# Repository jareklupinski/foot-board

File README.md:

# foot-board
A USB Keyboard Device, laid out to be used with your Feet

Uses Kailh Low Profile Switches, code written to be easy to jump into and modify.

Can be produced by JLCPCB for extremely low cost. Only thing they cannot do is solder the MicroUSB jack; considering laying out the PCB with a connector for an off-the-shelf Blue Pill board to fix.

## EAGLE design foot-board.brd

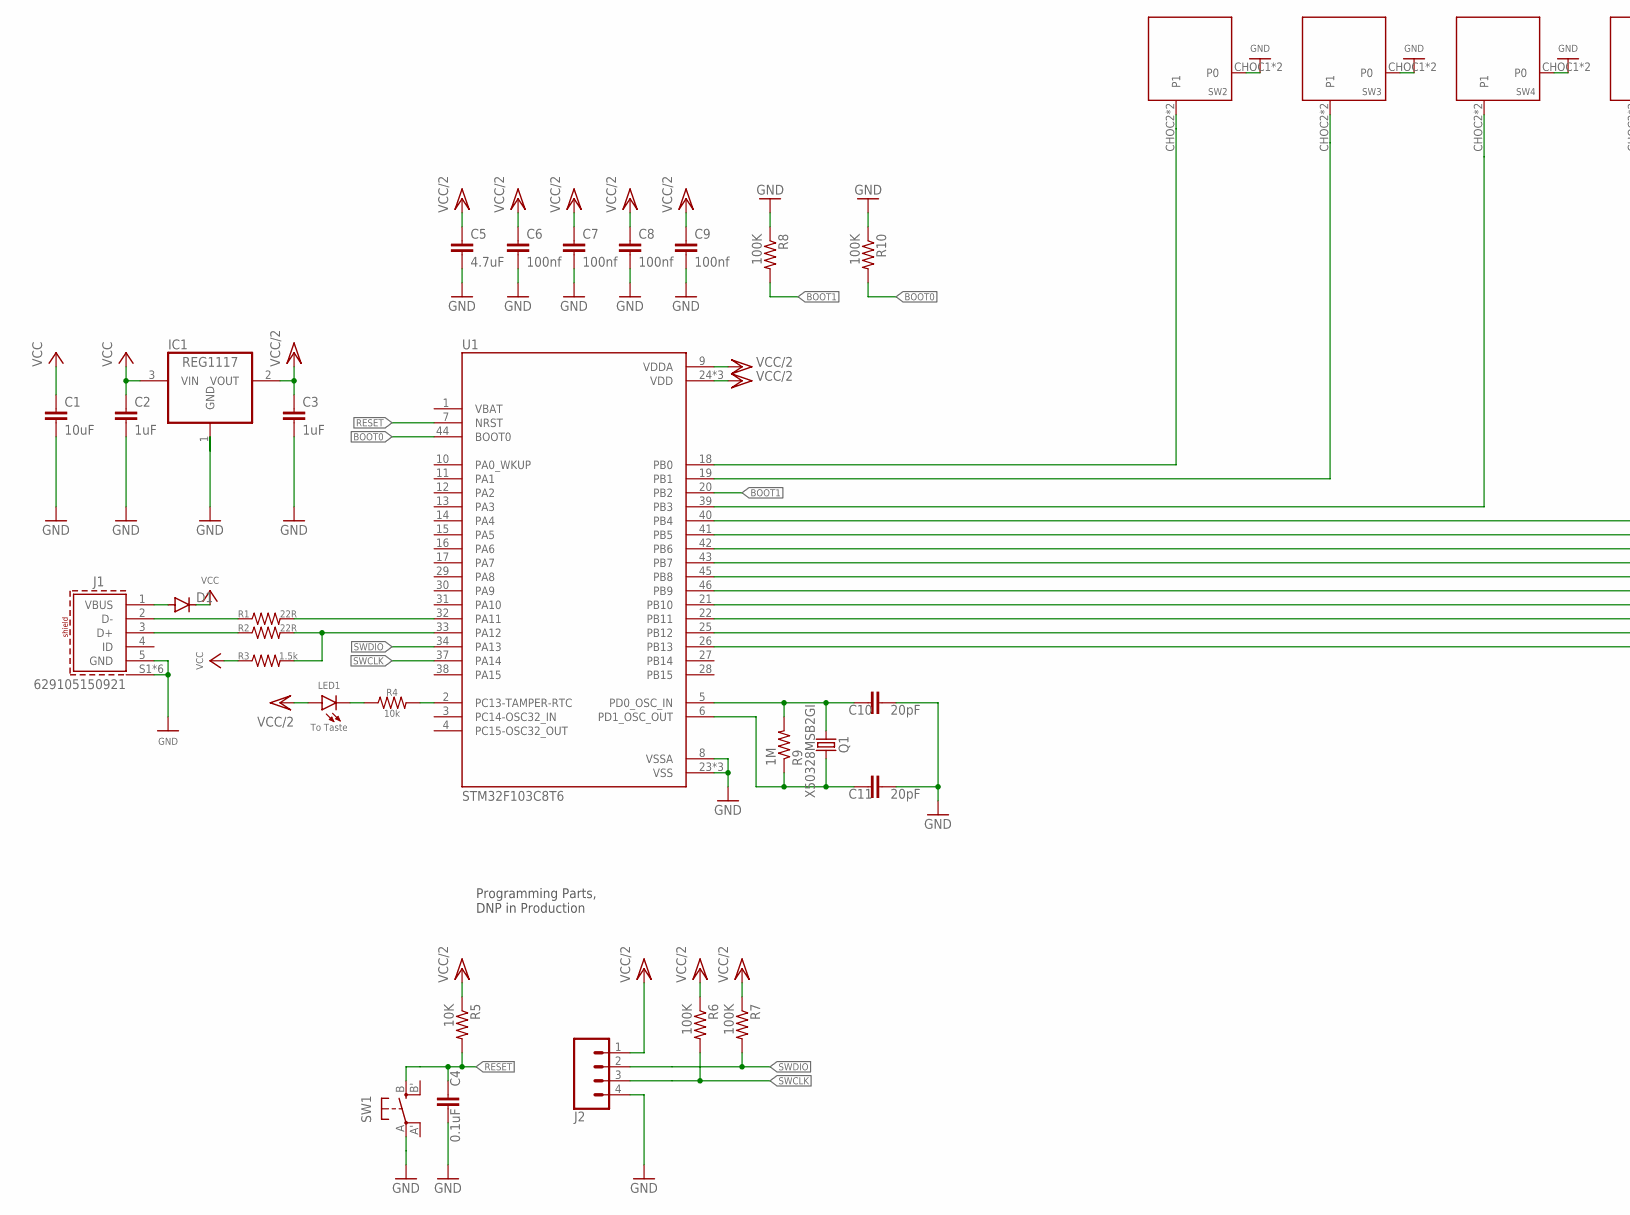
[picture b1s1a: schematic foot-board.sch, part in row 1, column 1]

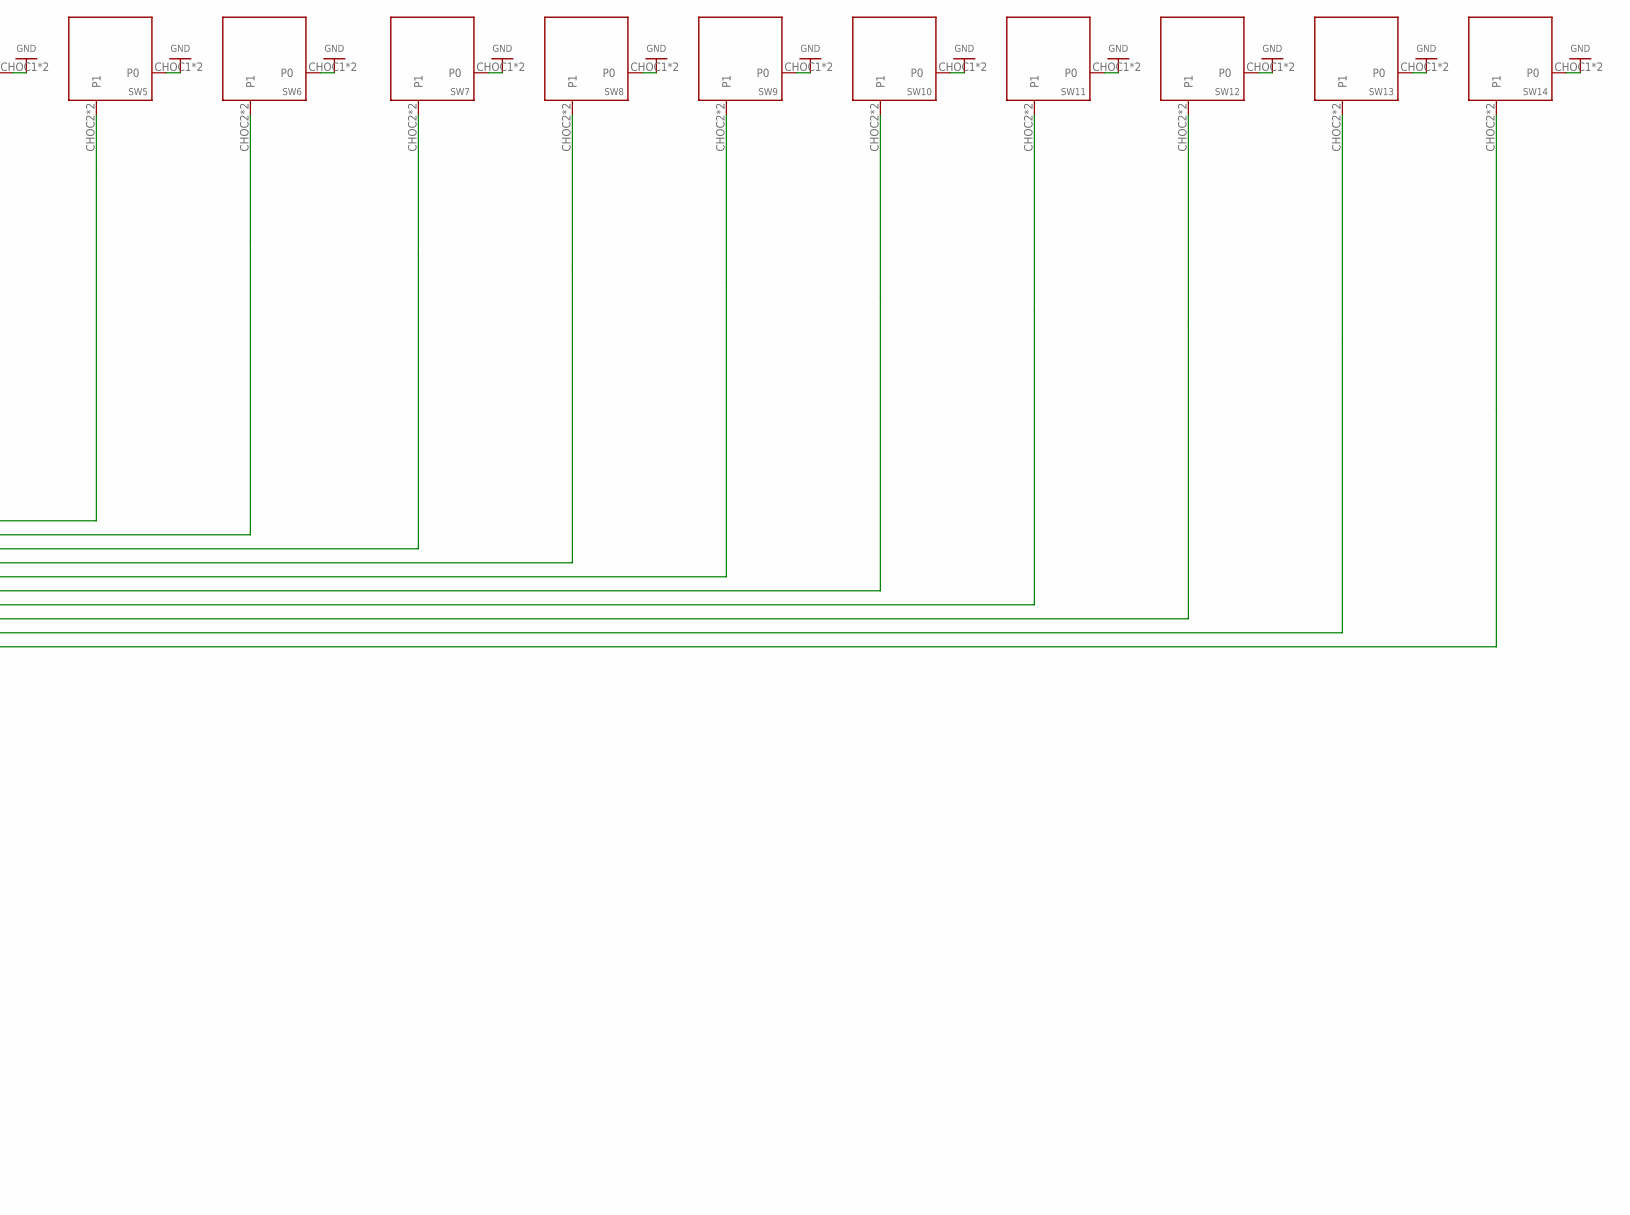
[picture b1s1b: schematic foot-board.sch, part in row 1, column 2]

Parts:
C1: 10uF; C0805
C2, C3: 1uF; C0402
C4: 0.1uF; C0402
C5: 4.7uF; C0805
C6, C7, C8, C9: 100nf; C0402
C10, C11: 20pF; C0402
D1: DIODE-DO214AC; DO214AC
IC1: REG1117; SOT223
J1: 629105150921
J2: CONN_04; 1X04
LED1: To Taste; CHIPLED_0603
Q1: X50328MSB2GI; 6.0X3.5_2
R1, R2: 22R; R0402
R3: 1.5k; R0402
R4: 10k; R0402
R5: 10K; R0402
R6, R7, R8, R10: 100K; R0402
R9: 1M; R0402
SW1: SPST_TACT-EVQQ2; EVQ-Q2
SW2, SW3, SW4, SW5, SW6, SW7, SW8, SW9, SW10, SW11, SW12, SW13, SW14: KEYSWITCH-PLAIN-CHOCX-1U; CHOCX-1U
U1: STM32F103C8T6; QFP50P900X900X160-48N

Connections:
BOOT0: R10.2, U1.44 (BOOT0)
BOOT1: R8.2, U1.20 (PB2)
GND: C1.2, C2.2, C3.2, C4.2, C5.2, C6.2, C7.2, C8.2, C9.2, C10.2, C11.2, IC1.1 (GND), J1.5 (GND), J1.S1 (SHIELD), J1.S2 (SHIELD), J1.S3 (SHIELD), J1.S4 (SHIELD), J1.S5 (SHIELD), J1.S6 (SHIELD), J2.4, R8.1, R10.1, SW1.A, SW2.CHOC1 (P0), SW2.X1 (P0), SW3.CHOC1 (P0), SW3.X1 (P0), SW4.CHOC1 (P0), SW4.X1 (P0), SW5.CHOC1 (P0), SW5.X1 (P0), SW6.CHOC1 (P0), SW6.X1 (P0), SW7.CHOC1 (P0), SW7.X1 (P0), SW8.CHOC1 (P0), SW8.X1 (P0), SW9.CHOC1 (P0), SW9.X1 (P0), SW10.CHOC1 (P0), SW10.X1 (P0), SW11.CHOC1 (P0), SW11.X1 (P0), SW12.CHOC1 (P0), SW12.X1 (P0), SW13.CHOC1 (P0), SW13.X1 (P0), SW14.CHOC1 (P0), SW14.X1 (P0), U1.8 (VSSA), U1.23 (VSS), U1.35 (VSS), U1.47 (VSS)
unnamed: R4.2, U1.2 (PC13-TAMPER-RTC)
unnamed: LED1.C, R4.1
unnamed: SW2.CHOC2 (P1), SW2.X2 (P1), U1.18 (PB0)
unnamed: R1.2, U1.32 (PA11)
unnamed: D1.A, J1.1 (VBUS)
unnamed: R2.2, R3.2, U1.33 (PA12)
unnamed: SW3.CHOC2 (P1), SW3.X2 (P1), U1.19 (PB1)
unnamed: SW4.CHOC2 (P1), SW4.X2 (P1), U1.39 (PB3)
unnamed: SW5.CHOC2 (P1), SW5.X2 (P1), U1.40 (PB4)
unnamed: SW6.CHOC2 (P1), SW6.X2 (P1), U1.41 (PB5)
unnamed: SW7.CHOC2 (P1), SW7.X2 (P1), U1.42 (PB6)
unnamed: SW8.CHOC2 (P1), SW8.X2 (P1), U1.43 (PB7)
unnamed: SW9.CHOC2 (P1), SW9.X2 (P1), U1.45 (PB8)
unnamed: SW10.CHOC2 (P1), SW10.X2 (P1), U1.46 (PB9)
unnamed: SW11.CHOC2 (P1), SW11.X2 (P1), U1.21 (PB10)
unnamed: J1.2 (D-), R1.1
unnamed: J1.3 (D+), R2.1
unnamed: SW12.CHOC2 (P1), SW12.X2 (P1), U1.22 (PB11)
unnamed: SW13.CHOC2 (P1), SW13.X2 (P1), U1.25 (PB12)
unnamed: SW14.CHOC2 (P1), SW14.X2 (P1), U1.26 (PB13)
unnamed: C10.1, Q1.2, R9.2, U1.5 (PD0_OSC_IN)
unnamed: C11.1, Q1.1, R9.1, U1.6 (PD1_OSC_OUT)
RESET: C4.1, R5.2, SW1.B (S), U1.7 (NRST)
SWCLK: J2.3, R6.2, U1.37 (PA14)
SWDIO: J2.2, R7.2, U1.34 (PA13)
VCC: C1.1, C2.1, D1.C, IC1.3 (VIN), R3.1
VCC/2: C3.1, C5.1, C6.1, C7.1, C8.1, C9.1, IC1.2 (VOUT), J2.1, LED1.A, R5.1, R6.1, R7.1, U1.9 (VDDA), U1.24 (VDD), U1.36 (VDD), U1.48 (VDD)

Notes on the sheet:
Programming Parts, DNP in Production

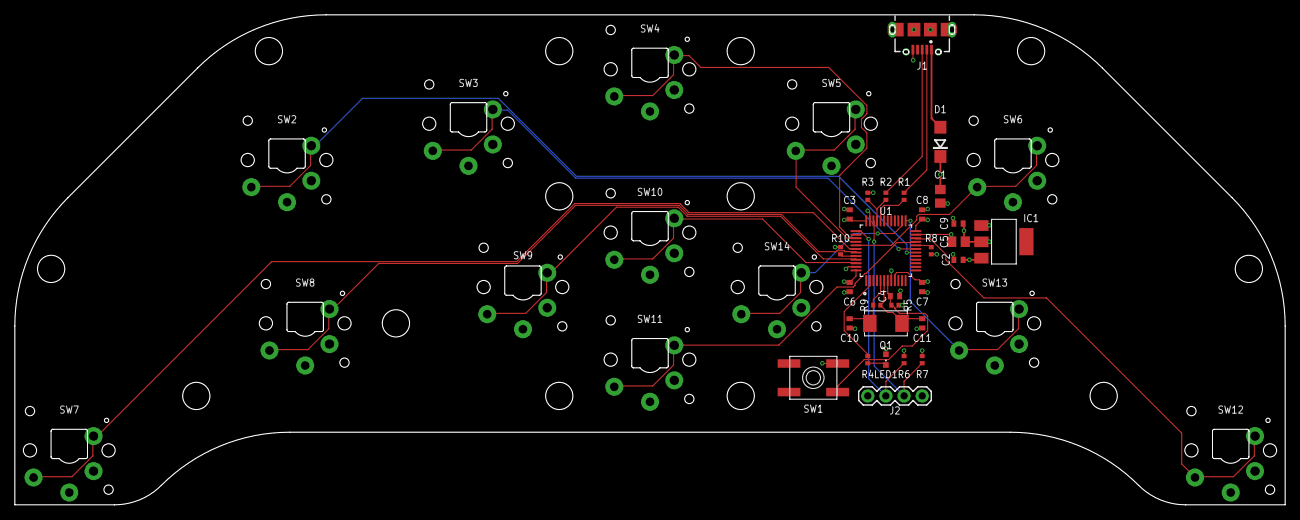
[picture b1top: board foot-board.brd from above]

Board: 4 copper layers, 177.8 x 68.6 mm, 42 parts (0 on the bottom side), 30 nets.

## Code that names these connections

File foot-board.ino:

#include "Keyboard.h"

void setup() {
  pinMode(PB0, INPUT_PULLUP);
  pinMode(PB1, INPUT_PULLUP);
  pinMode(PB3, INPUT_PULLUP);
  pinMode(PB4, INPUT_PULLUP);
  pinMode(PB5, INPUT_PULLUP);
  pinMode(PB6, INPUT_PULLUP);
  pinMode(PB7, INPUT_PULLUP);
  pinMode(PB8, INPUT_PULLUP);
  pinMode(PB9, INPUT_PULLUP);
  pinMode(PB10, INPUT_PULLUP);
  pinMode(PB11, INPUT_PULLUP);
  pinMode(PB12, INPUT_PULLUP);
  pinMode(PB13, INPUT_PULLUP);
  pinMode(PC13, OUTPUT);
  Keyboard.begin();
  digitalWrite(PC13, LOW);
}

byte button1Pressed = 0;
byte button2Pressed = 0;
byte button3Pressed = 0;
byte button4Pressed = 0;
byte button5Pressed = 0;
byte button6Pressed = 0;
byte button7Pressed = 0;
byte button8Pressed = 0;
byte button9Pressed = 0;
byte button10Pressed = 0;
byte button11Pressed = 0;
byte button12Pressed = 0;
byte button13Pressed = 0;

void loop() {
  byte newButton1Pressed = 0;
  if ( digitalReadFast(PB_0) ) newButton1Pressed = 1;
  if ( newButton1Pressed != button1Pressed ) {
    newButton1Pressed ? Keyboard.release('1') : Keyboard.press('1');
    button1Pressed = newButton1Pressed;
  }
  byte newButton2Pressed = 0;
  if ( digitalReadFast(PB_1) ) newButton2Pressed = 1;
  if ( newButton2Pressed != button2Pressed ) {
    newButton2Pressed ? Keyboard.release('2') : Keyboard.press('2');
    button2Pressed = newButton2Pressed;
  }
  byte newButton3Pressed = 0;
  if ( digitalReadFast(PB_3) ) newButton3Pressed = 1;
  if ( newButton3Pressed != button3Pressed ) {
    newButton3Pressed ? Keyboard.release('3') : Keyboard.press('3');
    button3Pressed = newButton3Pressed;
  }
  byte newButton4Pressed = 0;
  if ( digitalReadFast(PB_4) ) newButton4Pressed = 1;
  if ( newButton4Pressed != button4Pressed ) {
    newButton4Pressed ? Keyboard.release('4') : Keyboard.press('4');
    button4Pressed = newButton4Pressed;
  }
  byte newButton5Pressed = 0;
  if ( digitalReadFast(PB_5) ) newButton5Pressed = 1;
  if ( newButton5Pressed != button5Pressed ) {
    newButton5Pressed ? Keyboard.release('5') : Keyboard.press('5');
    button5Pressed = newButton5Pressed;
  }
  byte newButton6Pressed = 0;
  if ( digitalReadFast(PB_6) ) newButton6Pressed = 1;
  if ( newButton6Pressed != button6Pressed ) {
    newButton6Pressed ? Keyboard.release('z') : Keyboard.press('z');
    button6Pressed = newButton6Pressed;
  }
  byte newButton7Pressed = 0;
  if ( digitalReadFast(PB_7) ) newButton7Pressed = 1;
  if ( newButton7Pressed != button7Pressed ) {
    newButton7Pressed ? Keyboard.release('x') : Keyboard.press('x');
    button7Pressed = newButton7Pressed;
  }
  byte newButton8Pressed = 0;
  if ( digitalReadFast(PB_8) ) newButton8Pressed = 1;
  if ( newButton8Pressed != button8Pressed ) {
    newButton8Pressed ? Keyboard.release(KEY_LEFT_ARROW) : Keyboard.press(KEY_LEFT_ARROW);
    button8Pressed = newButton8Pressed;
  }
  byte newButton9Pressed = 0;
  if ( digitalReadFast(PB_9) ) newButton9Pressed = 1;
  if ( newButton9Pressed != button9Pressed ) {
    newButton9Pressed ? Keyboard.release(KEY_UP_ARROW) : Keyboard.press(KEY_UP_ARROW);
    button9Pressed = newButton9Pressed;
  }
  byte newButton10Pressed = 0;
  if ( digitalReadFast(PB_10) ) newButton10Pressed = 1;
  if ( newButton10Pressed != button10Pressed ) {
    newButton10Pressed ? Keyboard.release(KEY_DOWN_ARROW) : Keyboard.press(KEY_DOWN_ARROW);
    button10Pressed = newButton10Pressed;
  }
  byte newButton11Pressed = 0;
  if ( digitalReadFast(PB_11) ) newButton11Pressed = 1;
  if ( newButton11Pressed != button11Pressed ) {
    newButton11Pressed ? Keyboard.release('m') : Keyboard.press('m');
    button11Pressed = newButton11Pressed;
  }
  byte newButton12Pressed = 0;
  if ( digitalReadFast(PB_12) ) newButton12Pressed = 1;
  if ( newButton12Pressed != button12Pressed ) {
    newButton12Pressed ? Keyboard.release('n') : Keyboard.press('n');
    button12Pressed = newButton12Pressed;
  }
  byte newButton13Pressed = 0;
  if ( digitalReadFast(PB_13) ) newButton13Pressed = 1;
  if ( newButton13Pressed != button13Pressed ) {
    newButton13Pressed ? Keyboard.release(KEY_RIGHT_ARROW) : Keyboard.press(KEY_RIGHT_ARROW);
    button13Pressed = newButton13Pressed;
  }
}

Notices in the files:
parts and their libraries:
SparkFun-Connectors: Licensing: Creative Commons ShareAlike 4.0 International - https://creativecommons.org/licenses/by-sa/4.0
crystal-geyer_V1_0: Copyright: Geyer-Electronic
Wurth_Connectors_WR-USB: Copyright: Würth Elektronik
